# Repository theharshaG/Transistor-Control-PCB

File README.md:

# Transistor-Control-PCB

 Transistor LED Control PCB (KiCad)

## Description

This project demonstrates how to control an LED using an NPN transistor as a switch.

##  Components

* NPN Transistor (BC547 / 2N2222)
* LED
* Resistors (1k)
* Push Button
* Connector

##  Concept

A transistor is used as a switch:

* Button provides base signal
* Transistor turns ON
* LED glows

##  Output

### Schematic

### PCB Layout

### 3D View

##  Tool

KiCad

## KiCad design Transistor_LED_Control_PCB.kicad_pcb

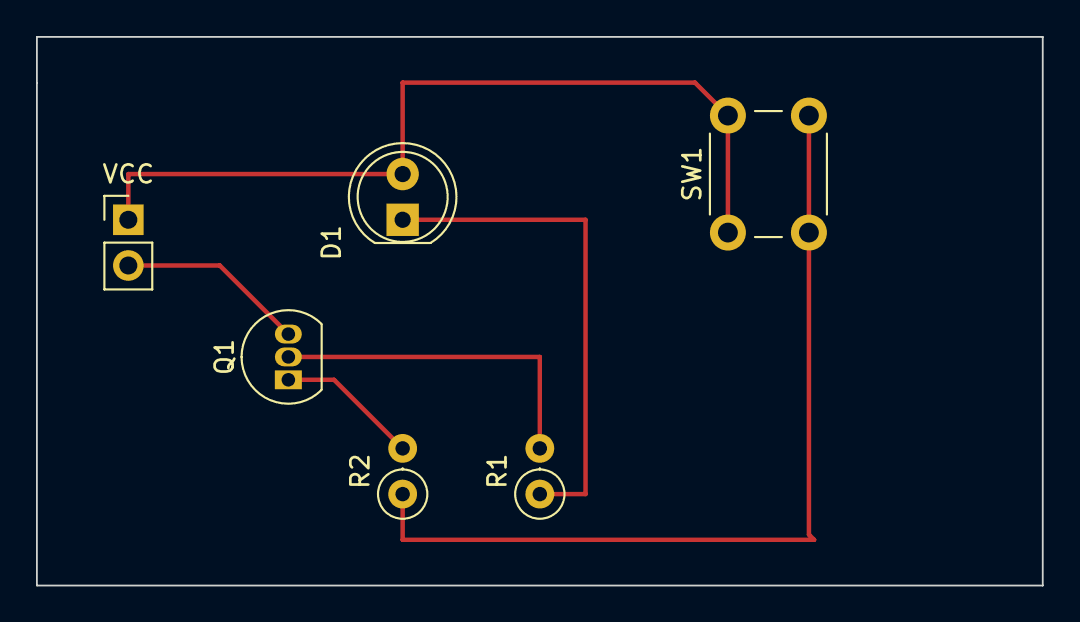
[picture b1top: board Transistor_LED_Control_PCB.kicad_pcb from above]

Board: 2 copper layers, 55.9 x 30.5 mm, 6 parts (0 on the bottom side), 6 nets.

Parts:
D1: LED; LED_D5.0mm
Q1: Q_NPN_BCE; TO-92_Inline
R1, R2: 1K; R_Axial_DIN0207_L6.3mm_D2.5mm_P2.54mm_Vertical
SW1: SW_Push; SW_PUSH_6mm
VCC: GND; PinHeader_1x02_P2.54mm_Vertical

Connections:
unnamed: D1.2 (A), SW1.1, VCC.1
unnamed: D1.1 (K), R1.1
unnamed: Q1.3 (E), VCC.2
unnamed: Q1.1 (B), R2.2
unnamed: Q1.2 (C), R1.2
unnamed: R2.1, SW1.2
